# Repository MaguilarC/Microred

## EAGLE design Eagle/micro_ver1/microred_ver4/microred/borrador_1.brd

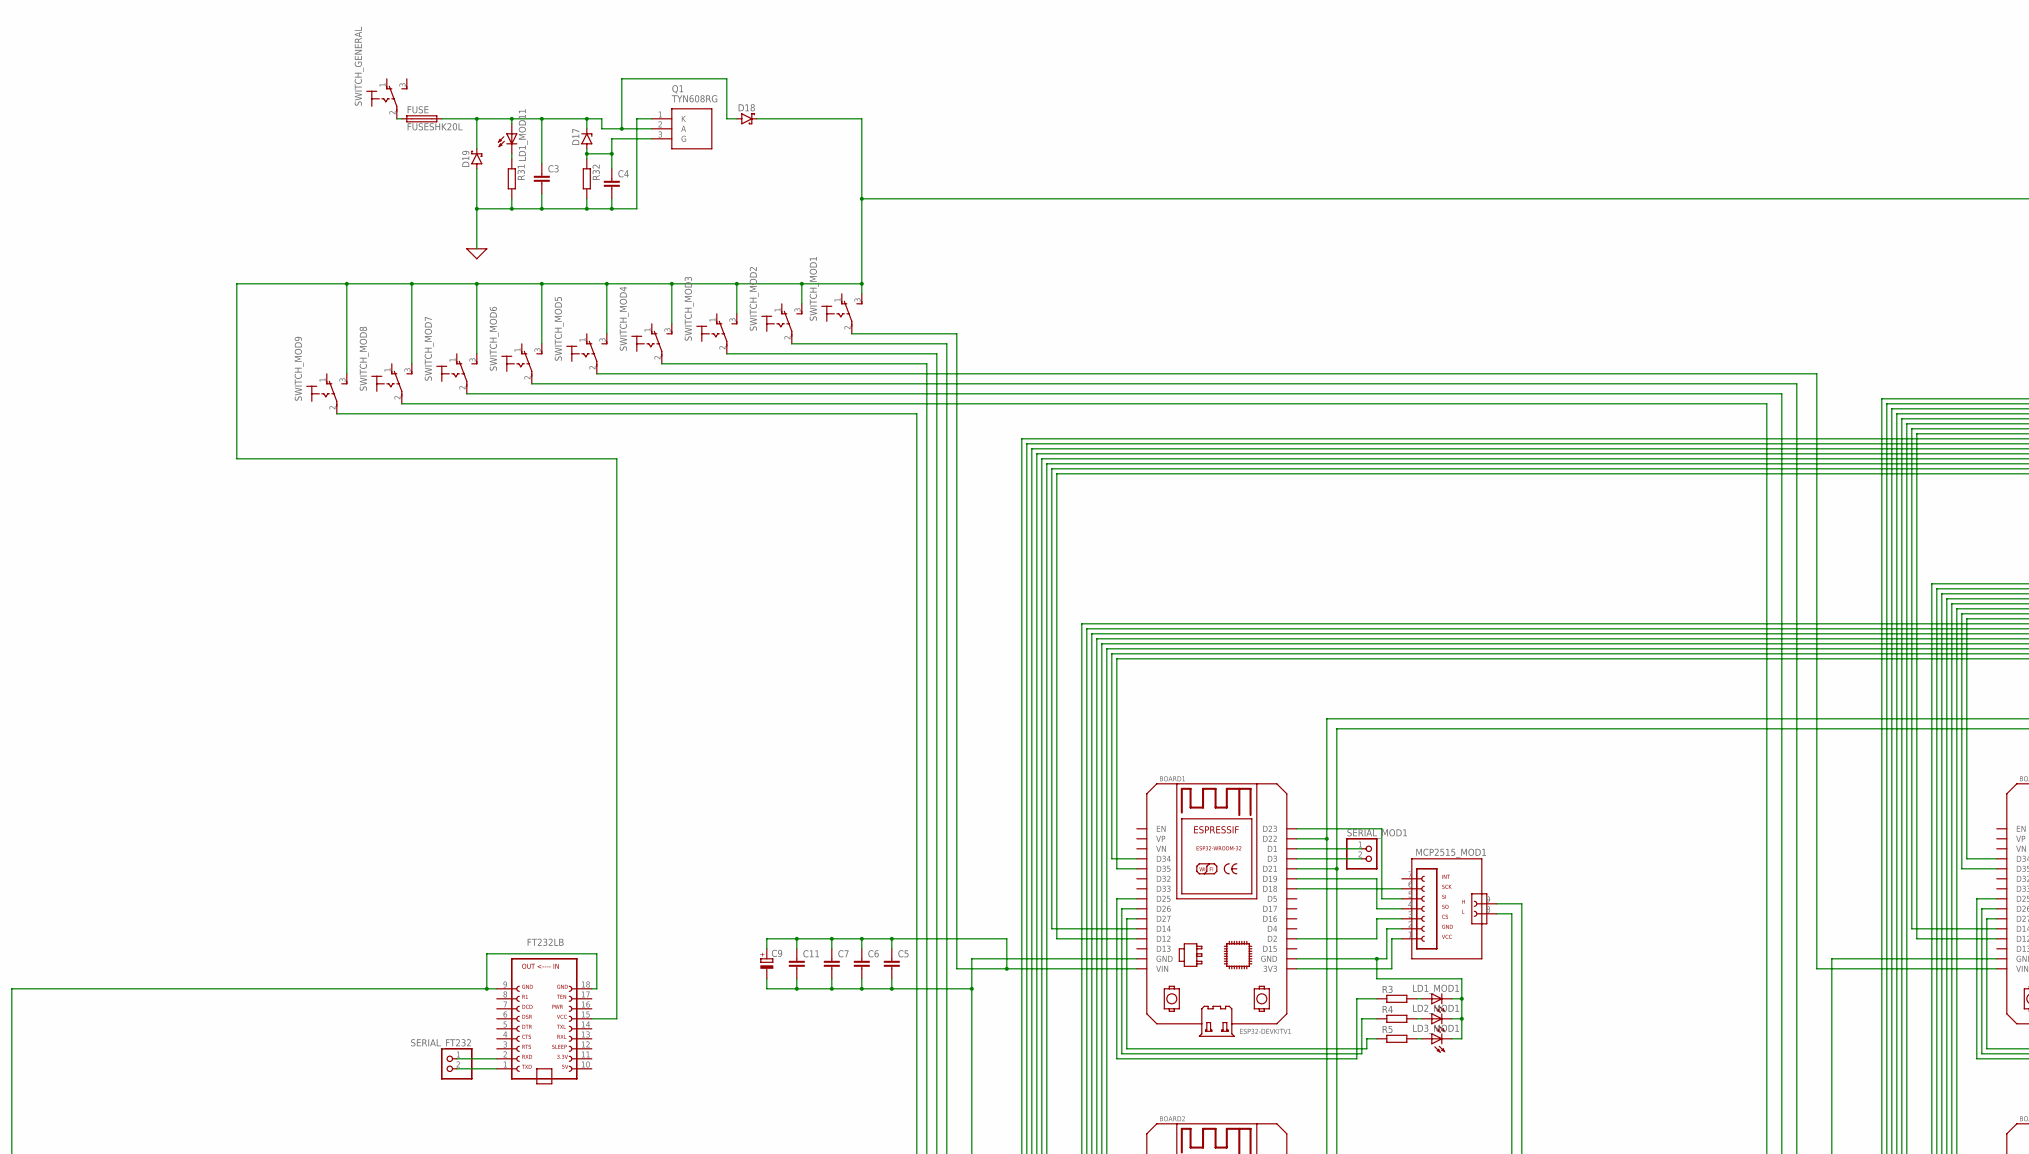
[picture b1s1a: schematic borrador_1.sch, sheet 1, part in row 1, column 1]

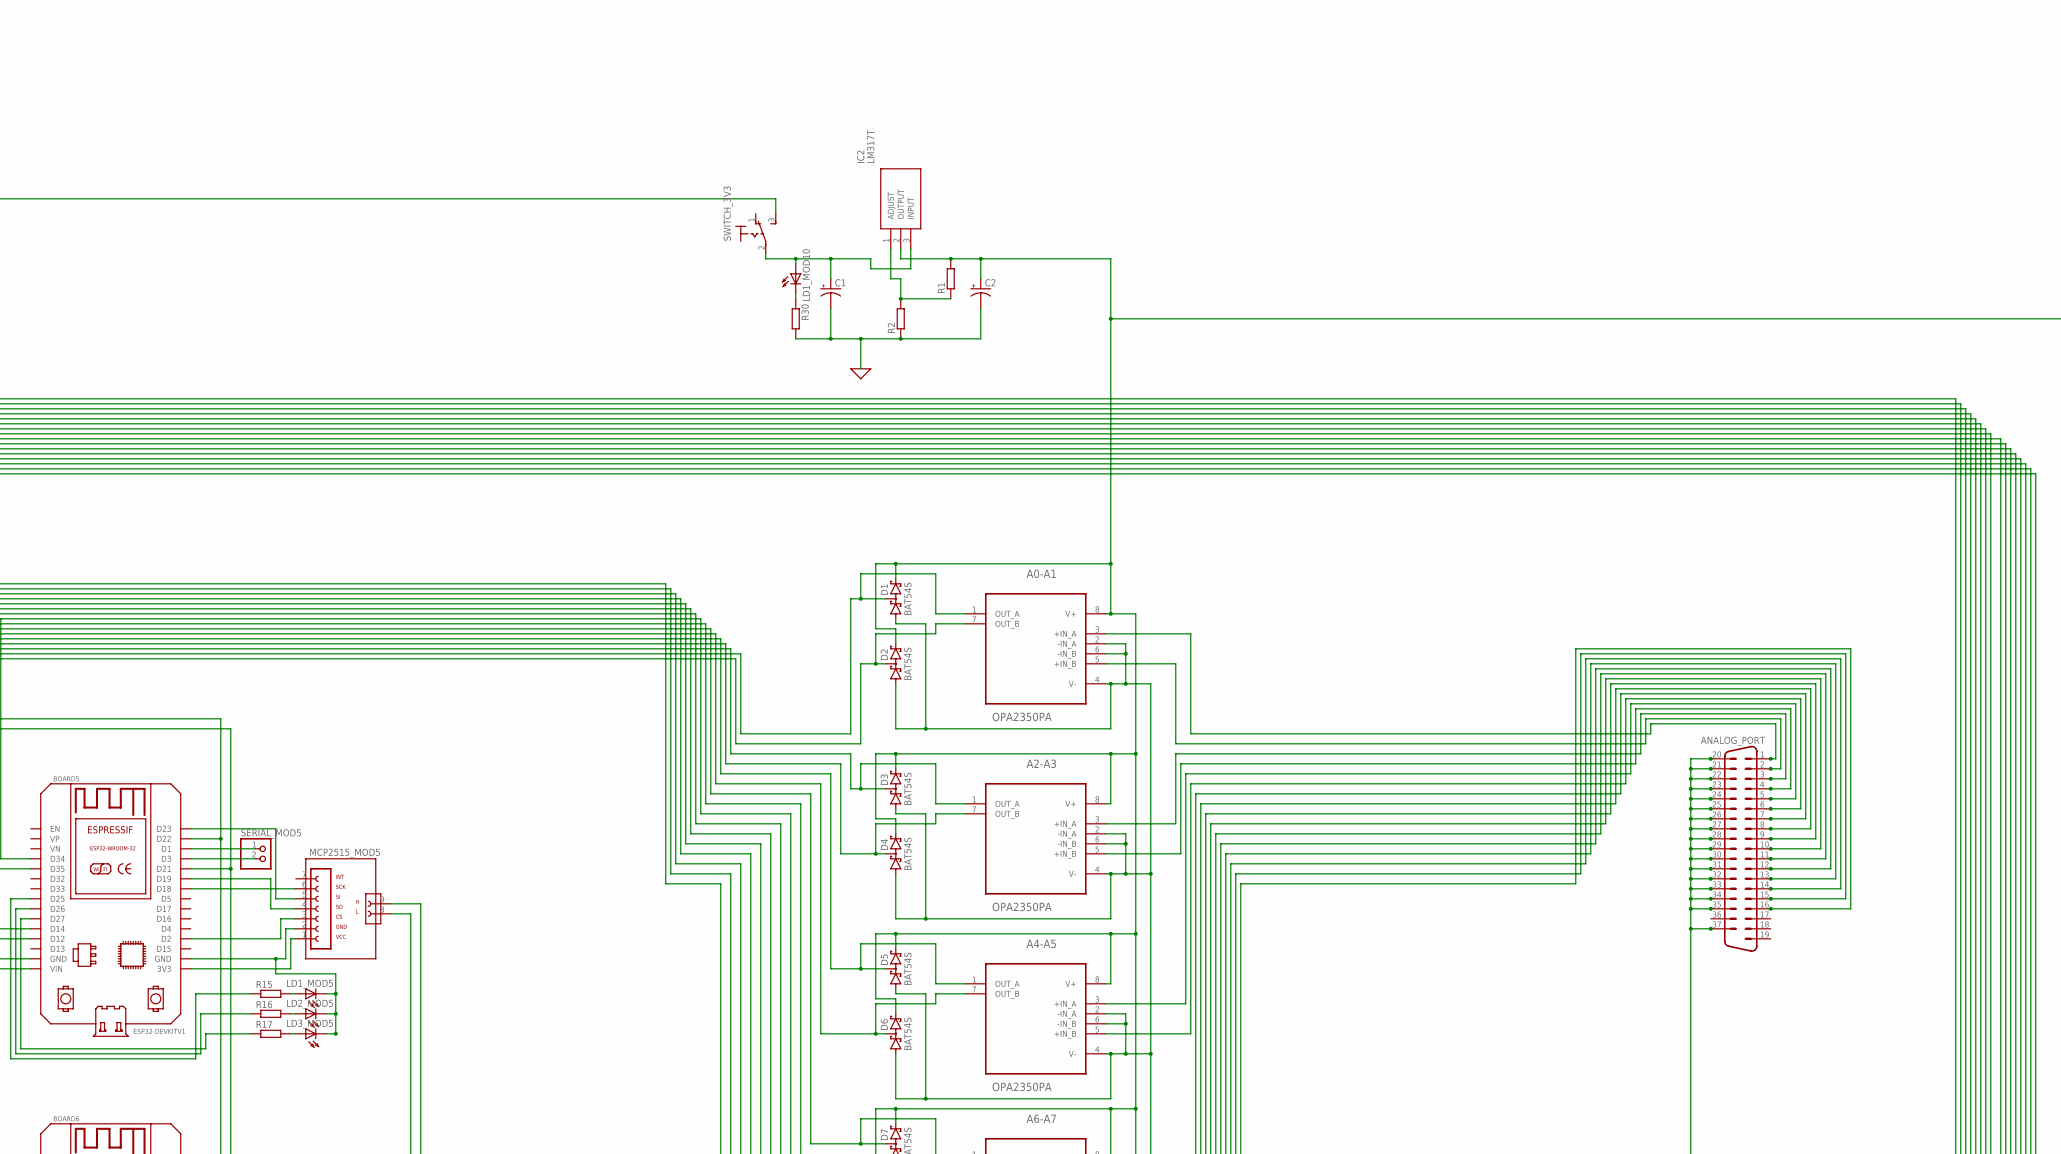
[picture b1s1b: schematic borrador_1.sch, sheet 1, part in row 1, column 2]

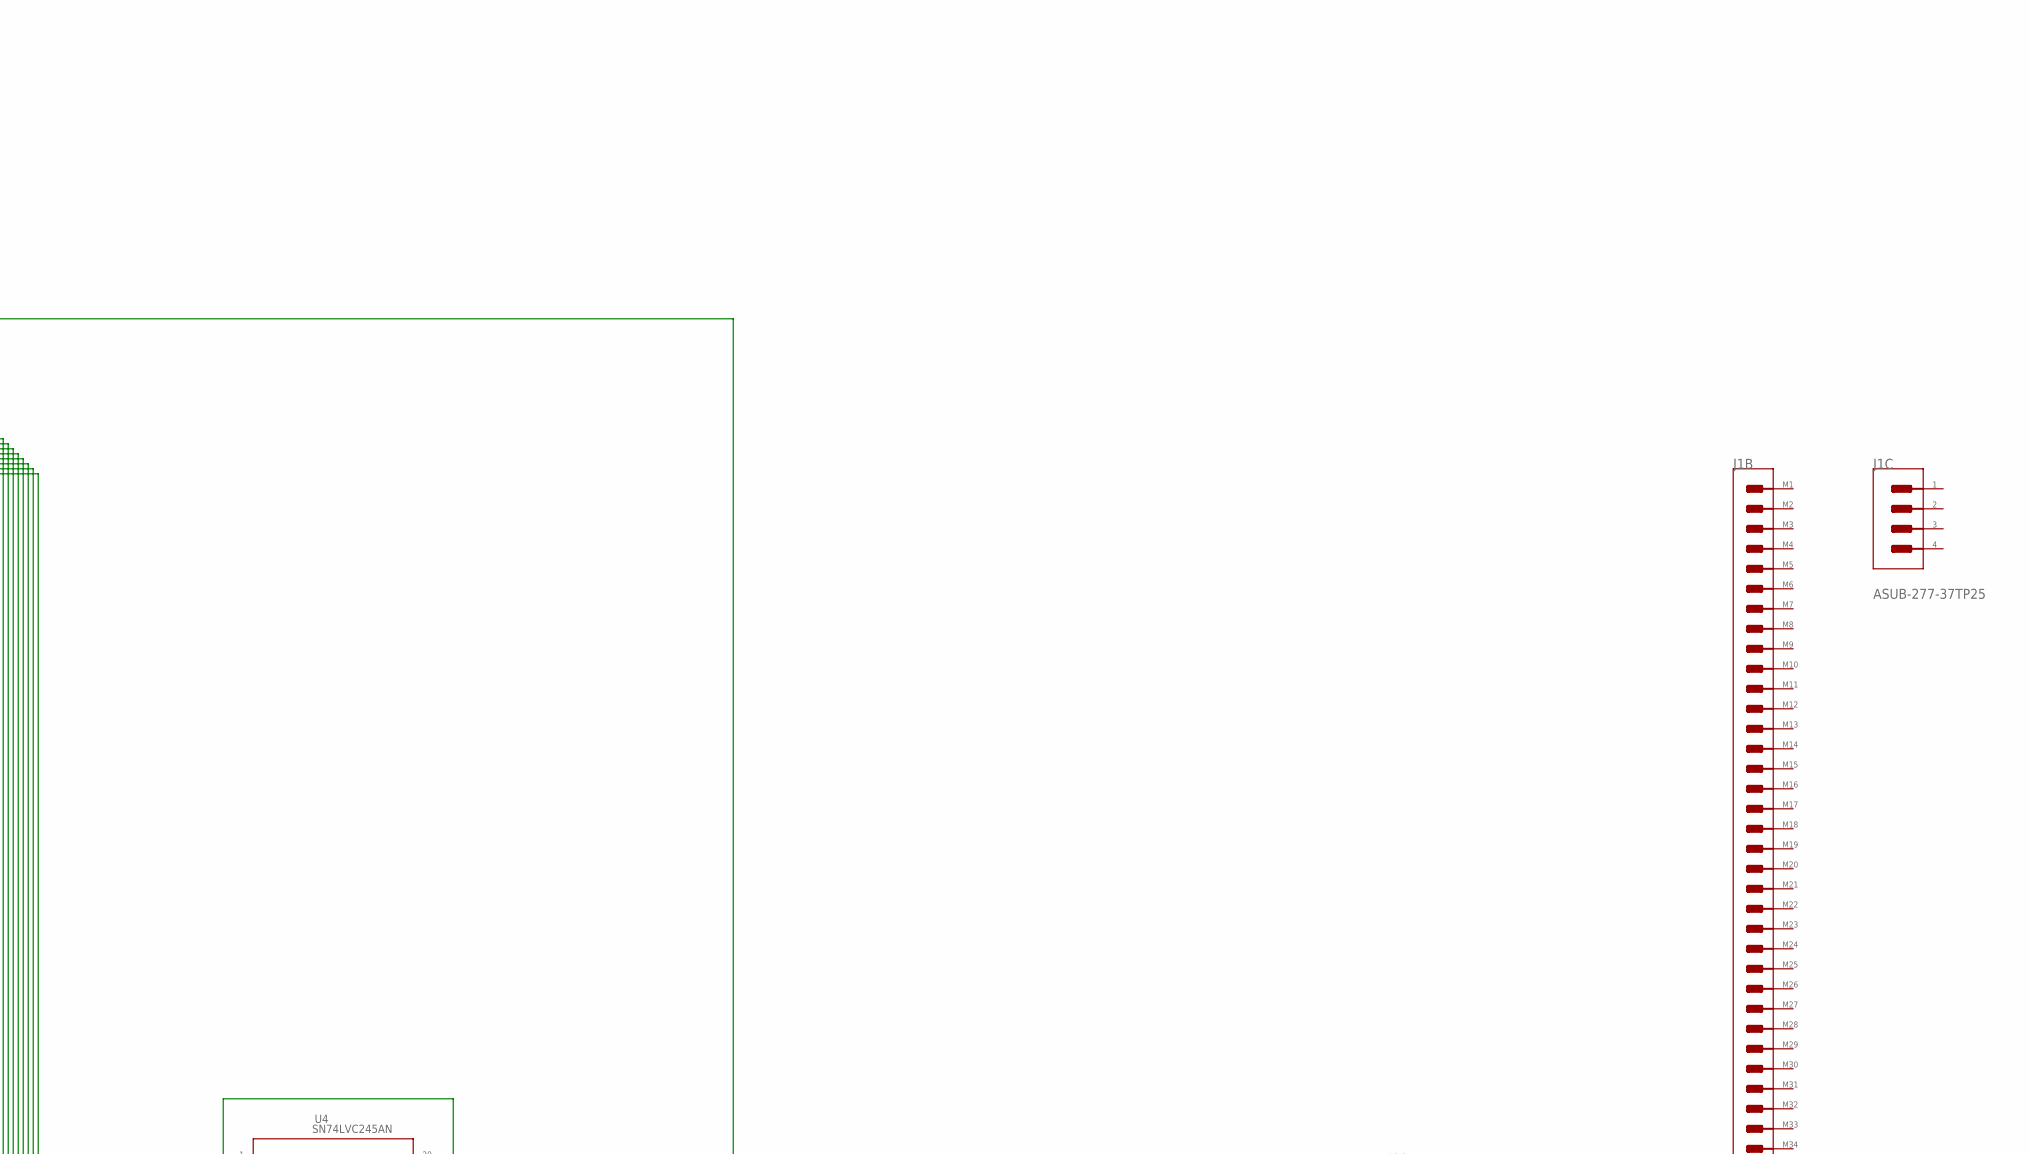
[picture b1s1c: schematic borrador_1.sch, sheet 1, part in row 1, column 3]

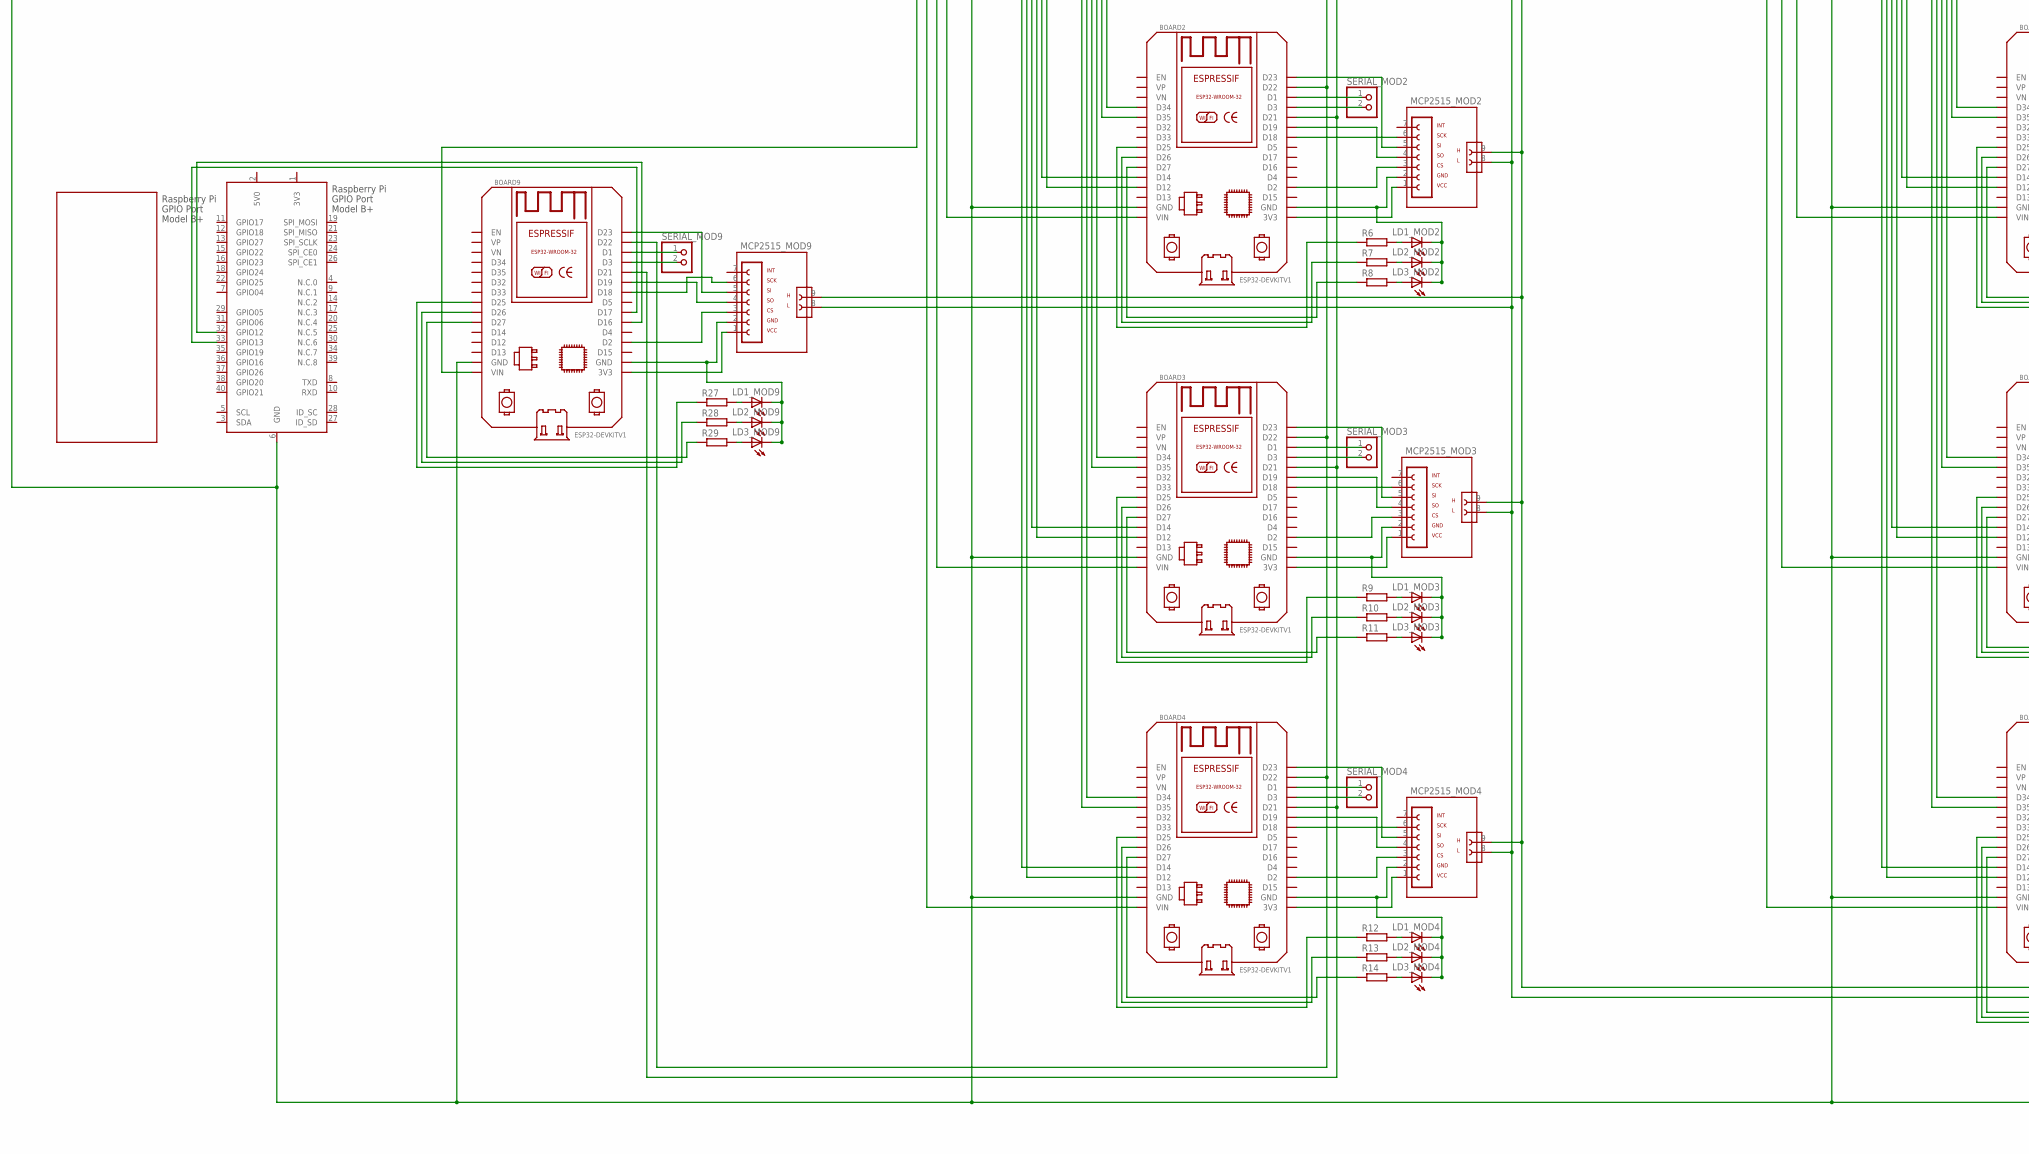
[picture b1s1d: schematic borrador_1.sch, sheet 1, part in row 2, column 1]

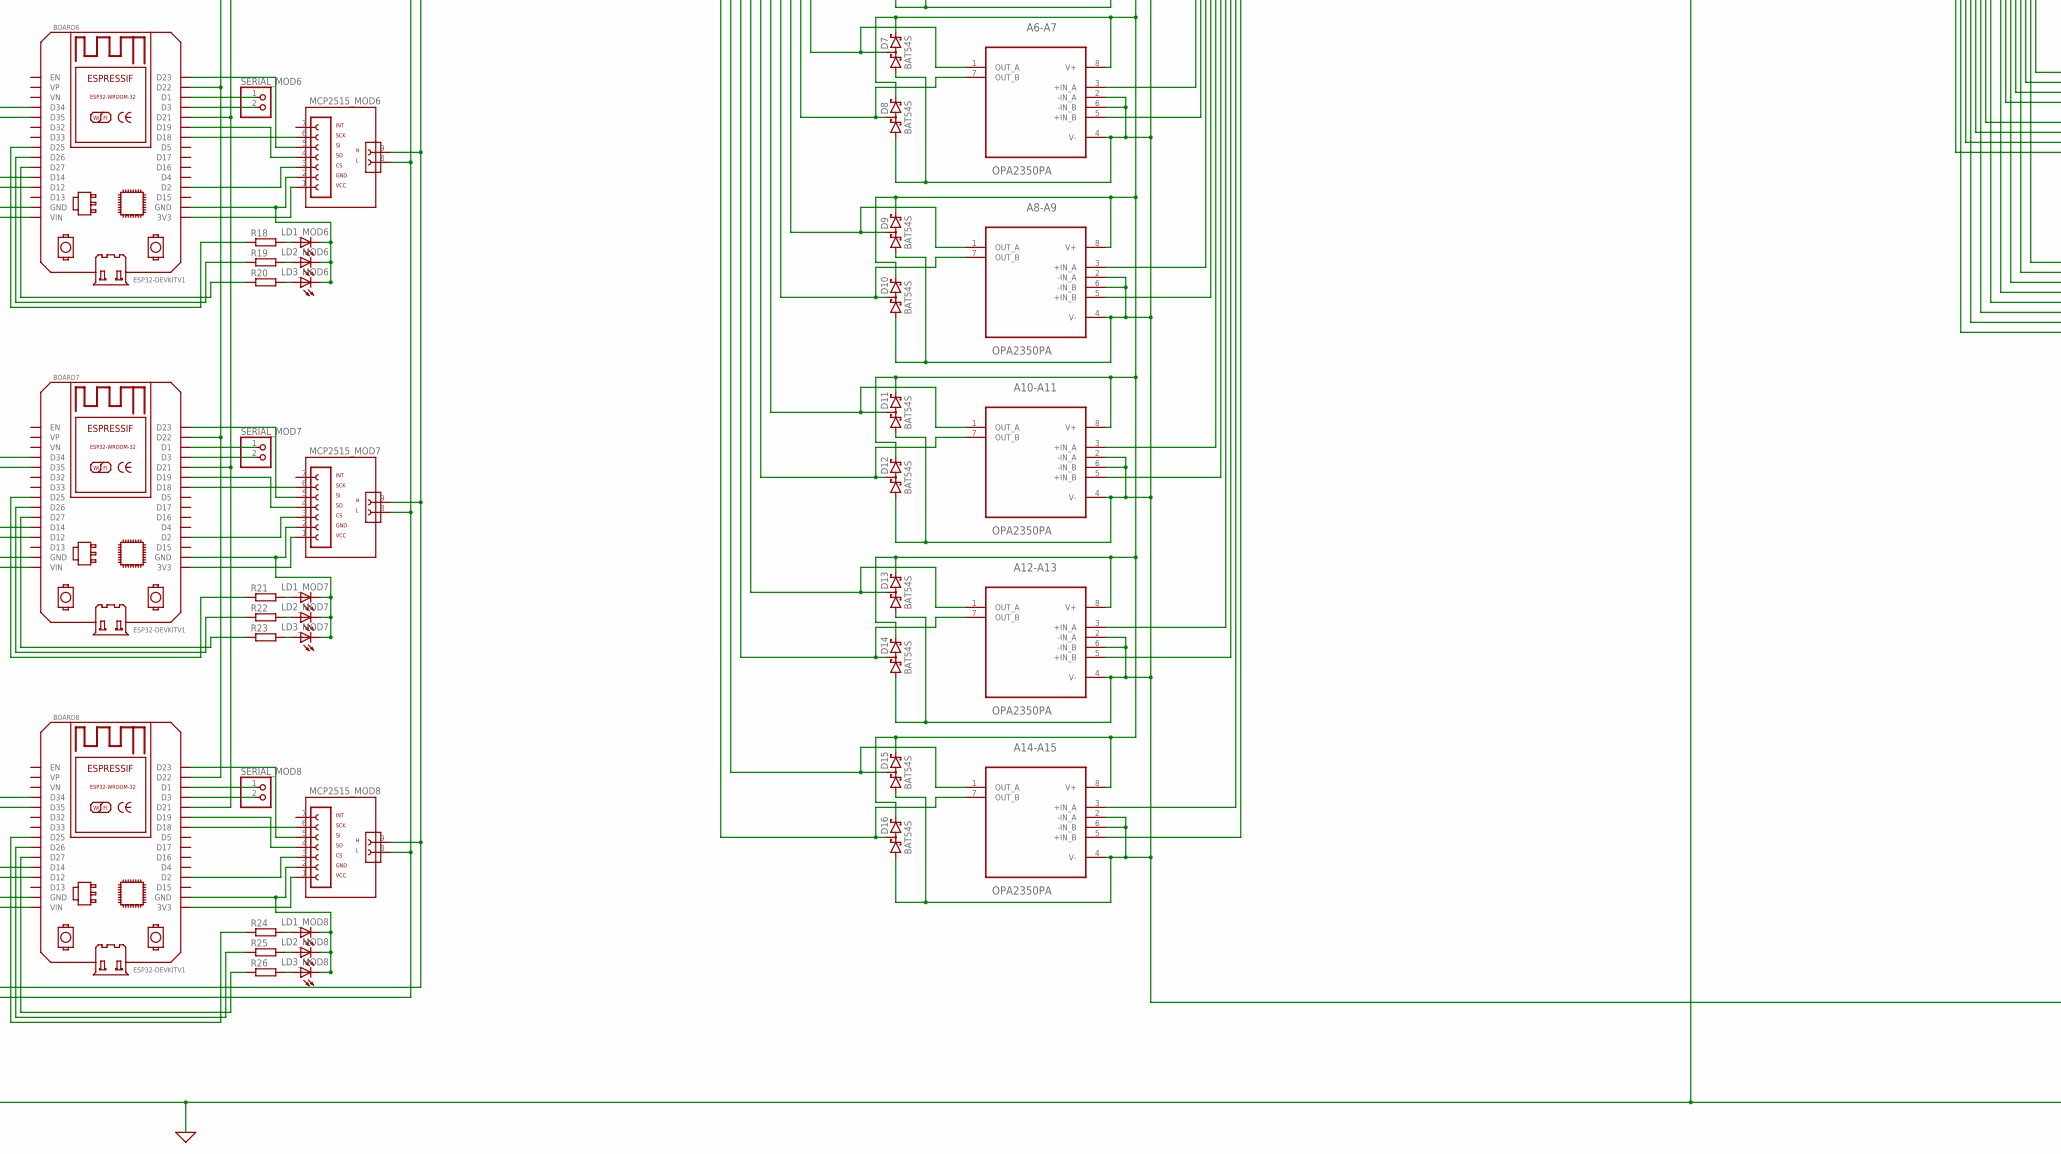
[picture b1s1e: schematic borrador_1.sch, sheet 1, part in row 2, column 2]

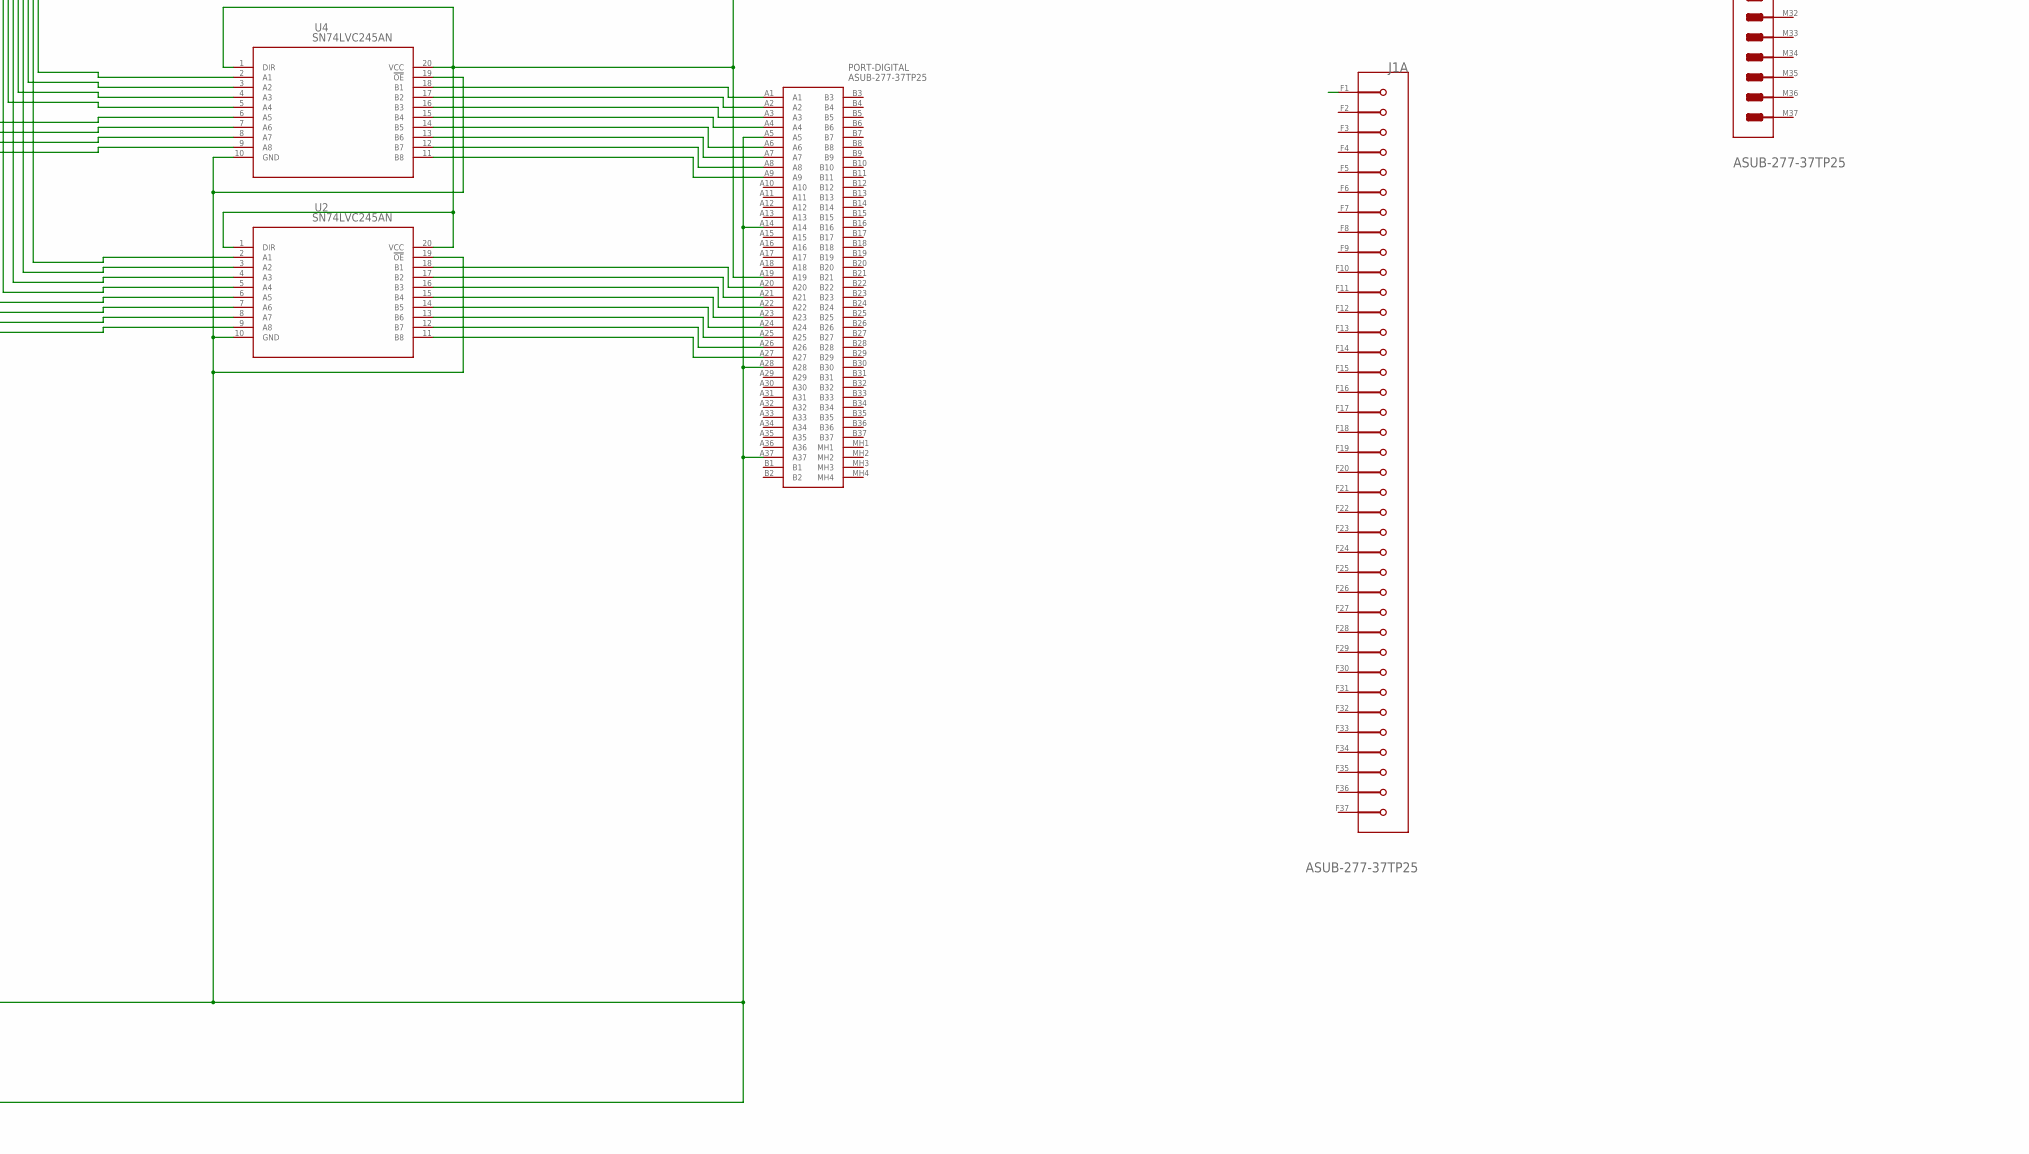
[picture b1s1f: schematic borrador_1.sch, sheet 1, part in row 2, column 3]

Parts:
A0-A1, A2-A3, A4-A5, A6-A7, A8-A9, A10-A11, A12-A13, A14-A15: OPA2350PA; DIP254P762X508-8
ANALOG_PORT: M37HP
BOARD1, BOARD2, BOARD3, BOARD4, BOARD5, BOARD6, BOARD7, BOARD8, BOARD9: ESP32DEVKITV1; ESP32-DEVKITV1
C1, C2: CPOL-USE2.5-6; E2,5-6
C3, C4, C11: C-EU050-030X075; C050-030X075
C5, C6: C2.5/2; C2.5-2
C7: C-EU025-030X050; C025-030X050
C9: CPOL-EUE2.5-6; E2,5-6
D1, D2, D3, D4, D5, D6, D7, D8, D9, D10, D11, D12, D13, D14, D15, D16: BAT54S; SOT23
D17: ZENER-DIODEDO41Z10; DO41Z10
D18, D19: SCHOTTKY-DIODECB429-15; CB429-15
FT232LB: FT232BL
FUSE: FUSESHK20L; SHK20L
IC2: LM317T; TO255P460X1020X2008-3P
J1: ASSMANN_WSW_COMPONENTS_ASUB-277-37TP25ASSMANN_WSW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; ASSMANN_WSW_COMPONENTS_ASUB-277-37TP25_0
LD1_MOD1, LD1_MOD2, LD1_MOD3, LD1_MOD4, LD1_MOD5, LD1_MOD6, LD1_MOD7, LD1_MOD8, LD1_MOD9, LD1_MOD10, LD1_MOD11, LD2_MOD1, LD2_MOD2, LD2_MOD3, LD2_MOD4, LD2_MOD5, LD2_MOD6, LD2_MOD7, LD2_MOD8, LD2_MOD9, LD3_MOD1, LD3_MOD2, LD3_MOD3, LD3_MOD4, LD3_MOD5, LD3_MOD6, LD3_MOD7, LD3_MOD8, LD3_MOD9: LED3MM
MCP2515_MOD1, MCP2515_MOD2, MCP2515_MOD3, MCP2515_MOD4, MCP2515_MOD5, MCP2515_MOD6, MCP2515_MOD7, MCP2515_MOD8, MCP2515_MOD9: MCP2515
PORT-DIGITAL: ASUB-277-37TP25; ASUB27737TP25
Q1: TYN608RG; TO270P460X1020X2008-3P
R1, R2: R-EU_0411/15; 0411/15
R3, R4, R5, R6, R7, R8, R9, R10, R11, R12, R13, R14, R15, R16, R17, R18, R19, R20, R21, R22, R23, R24, R25, R26, R27, R28, R29, R30, R31, R32: R-EU_0207/10; 0207/10
SERIAL_FT232: PINHD-1X2; 1X02
SERIAL_MOD1, SERIAL_MOD2, SERIAL_MOD3, SERIAL_MOD4, SERIAL_MOD5, SERIAL_MOD6, SERIAL_MOD7, SERIAL_MOD8, SERIAL_MOD9: PINHD-1X2; 1X02
SWITCH_3V3: M9040P
SWITCH_GENERAL: M9040P
SWITCH_MOD1, SWITCH_MOD2, SWITCH_MOD3, SWITCH_MOD4, SWITCH_MOD5, SWITCH_MOD6, SWITCH_MOD7, SWITCH_MOD8, SWITCH_MOD9: M9040P
U2, U4: SN74LVC245AN; N20
X1: RASPI_GPIO_B+_BOX
X2: RASPI_BOARD_B+#_F; RASPI_BOARD_B+_FULL

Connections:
3V3: X1.1 (3V3)
5V: D18.C, FT232LB.15, SWITCH_3V3.3 (S), SWITCH_MOD1.3 (S), SWITCH_MOD2.3 (S), SWITCH_MOD3.3 (S), SWITCH_MOD4.3 (S), SWITCH_MOD5.3 (S), SWITCH_MOD6.3 (S), SWITCH_MOD7.3 (S), SWITCH_MOD8.3 (S), SWITCH_MOD9.3 (S)
5V0: X1.2 (5V0)
5V_MOD1: BOARD1.VIN, C5.1, C6.1, C7.1, C9.+, C11.1, SWITCH_MOD1.2
5V_MOD2: BOARD2.VIN, SWITCH_MOD2.2
5V_MOD3: BOARD3.VIN, SWITCH_MOD3.2
5V_MOD4: BOARD4.VIN, SWITCH_MOD4.2
5V_MOD5: BOARD5.VIN, SWITCH_MOD5.2
5V_MOD6: BOARD6.VIN, SWITCH_MOD6.2
5V_MOD7: BOARD7.VIN, SWITCH_MOD7.2
5V_MOD8: BOARD8.VIN, SWITCH_MOD8.2
5V_MOD9: BOARD9.VIN, SWITCH_MOD9.2
CAN_H: MCP2515_MOD1.9, MCP2515_MOD2.9, MCP2515_MOD3.9, MCP2515_MOD4.9, MCP2515_MOD5.9, MCP2515_MOD6.9, MCP2515_MOD7.9, MCP2515_MOD8.9, MCP2515_MOD9.9
CAN_L: MCP2515_MOD1.8, MCP2515_MOD2.8, MCP2515_MOD3.8, MCP2515_MOD4.8, MCP2515_MOD5.8, MCP2515_MOD6.8, MCP2515_MOD7.8, MCP2515_MOD8.8, MCP2515_MOD9.8
GND_MOD1: BOARD1.GND@1 (GND), LD1_MOD1.K (C), LD2_MOD1.K (C), LD3_MOD1.K (C), MCP2515_MOD1.2
GND_MOD2: BOARD2.GND@1 (GND), LD1_MOD2.K (C), LD2_MOD2.K (C), LD3_MOD2.K (C), MCP2515_MOD2.2
GND_MOD3: BOARD3.GND@1 (GND), LD1_MOD3.K (C), LD2_MOD3.K (C), LD3_MOD3.K (C), MCP2515_MOD3.2
GND_MOD4: BOARD4.GND@1 (GND), LD1_MOD4.K (C), LD2_MOD4.K (C), LD3_MOD4.K (C), MCP2515_MOD4.2
GND_MOD5: BOARD5.GND@1 (GND), LD1_MOD5.K (C), LD2_MOD5.K (C), LD3_MOD5.K (C), MCP2515_MOD5.2
GND_MOD6: BOARD6.GND@1 (GND), LD1_MOD6.K (C), LD2_MOD6.K (C), LD3_MOD6.K (C), MCP2515_MOD6.2
GND_MOD7: BOARD7.GND@1 (GND), LD1_MOD7.K (C), LD2_MOD7.K (C), LD3_MOD7.K (C), MCP2515_MOD7.2
GND_MOD8: BOARD8.GND@1 (GND), LD1_MOD8.K (C), LD2_MOD8.K (C), LD3_MOD8.K (C), MCP2515_MOD8.2
GND_MOD9: BOARD9.GND@1 (GND), LD1_MOD9.K (C), LD2_MOD9.K (C), LD3_MOD9.K (C), MCP2515_MOD9.2
L_3V3: A0-A1.8 (V+), A2-A3.8 (V+), A4-A5.8 (V+), A6-A7.8 (V+), A8-A9.8 (V+), A10-A11.8 (V+), A12-A13.8 (V+), A14-A15.8 (V+), C2.+, D1.2 (C2), D2.2 (C2), D3.2 (C2), D4.2 (C2), D5.2 (C2), D6.2 (C2), D7.2 (C2), D8.2 (C2), D9.2 (C2), D10.2 (C2), D11.2 (C2), D12.2 (C2), D13.2 (C2), D14.2 (C2), D15.2 (C2), D16.2 (C2), IC2.2 (OUTPUT), PORT-DIGITAL.A19, R1.2, U2.1 (DIR), U2.20 (VCC), U4.1 (DIR), U4.20 (VCC)
L_AO_0: A0-A1.1 (OUT_A), BOARD1.D34, D1.3 (C1A2)
L_AO_0_P: A0-A1.3 (+IN_A), ANALOG_PORT.1
L_AO_1: A0-A1.7 (OUT_B), BOARD1.D35, D2.3 (C1A2)
L_AO_1_P: A0-A1.5 (+IN_B), ANALOG_PORT.2
L_AO_2: A2-A3.1 (OUT_A), BOARD2.D34, D3.3 (C1A2)
L_AO_2_P: A2-A3.3 (+IN_A), ANALOG_PORT.3
L_AO_3: A2-A3.7 (OUT_B), BOARD2.D35, D4.3 (C1A2)
L_AO_3_P: A2-A3.5 (+IN_B), ANALOG_PORT.4
L_AO_4: A4-A5.1 (OUT_A), BOARD3.D34, D5.3 (C1A2)
L_AO_4_P: A4-A5.3 (+IN_A), ANALOG_PORT.5
L_AO_5: A4-A5.7 (OUT_B), BOARD3.D35, D6.3 (C1A2)
L_AO_5_P: A4-A5.5 (+IN_B), ANALOG_PORT.6
L_AO_6: A6-A7.1 (OUT_A), BOARD4.D34, D7.3 (C1A2)
L_AO_6_P: A6-A7.3 (+IN_A), ANALOG_PORT.7
L_AO_7: A6-A7.7 (OUT_B), BOARD4.D35, D8.3 (C1A2)
L_AO_7_P: A6-A7.5 (+IN_B), ANALOG_PORT.8
L_AO_8: A8-A9.1 (OUT_A), BOARD5.D34, D9.3 (C1A2)
L_AO_8_P: A8-A9.3 (+IN_A), ANALOG_PORT.9
L_AO_9: A8-A9.7 (OUT_B), BOARD5.D35, D10.3 (C1A2)
L_AO_9_P: A8-A9.5 (+IN_B), ANALOG_PORT.10
L_AO_10: A10-A11.1 (OUT_A), BOARD6.D34, D11.3 (C1A2)
L_AO_10_P: A10-A11.3 (+IN_A), ANALOG_PORT.11
L_AO_11: A10-A11.7 (OUT_B), BOARD6.D35, D12.3 (C1A2)
L_AO_11_P: A10-A11.5 (+IN_B), ANALOG_PORT.12
L_AO_12: A12-A13.1 (OUT_A), BOARD7.D34, D13.3 (C1A2)
L_AO_12_P: A12-A13.3 (+IN_A), ANALOG_PORT.13
L_AO_13: A12-A13.7 (OUT_B), BOARD7.D35, D14.3 (C1A2)
L_AO_13_P: A12-A13.5 (+IN_B), ANALOG_PORT.14
L_AO_14: A14-A15.1 (OUT_A), BOARD8.D34, D15.3 (C1A2)
L_AO_14_P: A14-A15.3 (+IN_A), ANALOG_PORT.15
L_AO_15: A14-A15.7 (OUT_B), BOARD8.D35, D16.3 (C1A2)
L_AO_15_P: A14-A15.5 (+IN_B), ANALOG_PORT.16
L_DI_0: BOARD1.D12, U4.2 (A1)
L_DI_0_P: PORT-DIGITAL.A1, U4.18 (B1)
L_DI_1: BOARD1.D14, U2.2 (A1)
L_DI_1_P: PORT-DIGITAL.A20, U2.18 (B1)
L_DI_2: BOARD2.D12, U4.3 (A2)
L_DI_2_P: PORT-DIGITAL.A2, U4.17 (B2)
L_DI_3: BOARD2.D14, U2.3 (A2)
L_DI_3_P: PORT-DIGITAL.A21, U2.17 (B2)
L_DI_4: BOARD3.D12, U4.4 (A3)
L_DI_4_P: PORT-DIGITAL.A3, U4.16 (B3)
L_DI_5: BOARD3.D14, U2.4 (A3)
L_DI_5_P: PORT-DIGITAL.A22, U2.16 (B3)
L_DI_6: BOARD4.D12, U4.5 (A4)
L_DI_6_P: PORT-DIGITAL.A4, U4.15 (B4)
L_DI_7: BOARD4.D14, U2.5 (A4)
L_DI_7_P: PORT-DIGITAL.A23, U2.15 (B4)
L_DI_8: BOARD5.D12, U2.6 (A5)
L_DI_8_P: PORT-DIGITAL.A24, U2.14 (B5)
L_DI_9: BOARD5.D14, U4.6 (A5)
L_DI_9_P: PORT-DIGITAL.A6, U4.14 (B5)
L_DI_10: BOARD6.D12, U2.7 (A6)
L_DI_10_P: PORT-DIGITAL.A25, U2.13 (B6)
L_DI_11: BOARD6.D14, U4.7 (A6)
L_DI_11_P: PORT-DIGITAL.A7, U4.13 (B6)
L_DI_012: BOARD7.D12, U2.8 (A7)
L_DI_12_P: PORT-DIGITAL.A26, U2.12 (B7)
L_DI_13: BOARD7.D14, U4.8 (A7)
L_DI_13_P: PORT-DIGITAL.A8, U4.12 (B7)
L_DI_014: BOARD8.D12, U2.9 (A8)
L_DI_14_P: PORT-DIGITAL.A27, U2.11 (B8)
L_DI_015: BOARD8.D14, U4.9 (A8)
L_DI_15_P: PORT-DIGITAL.A9, U4.11 (B8)
L_GROUND: A0-A1.2 (-IN_A), A0-A1.4 (V-), A0-A1.6 (-IN_B), A2-A3.2 (-IN_A), A2-A3.4 (V-), A2-A3.6 (-IN_B), A4-A5.2 (-IN_A), A4-A5.4 (V-), A4-A5.6 (-IN_B), A6-A7.2 (-IN_A), A6-A7.4 (V-), A6-A7.6 (-IN_B), A8-A9.2 (-IN_A), A8-A9.4 (V-), A8-A9.6 (-IN_B), A10-A11.2 (-IN_A), A10-A11.4 (V-), A10-A11.6 (-IN_B), A12-A13.2 (-IN_A), A12-A13.4 (V-), A12-A13.6 (-IN_B), A14-A15.2 (-IN_A), A14-A15.4 (V-), A14-A15.6 (-IN_B), ANALOG_PORT.20, ANALOG_PORT.21, ANALOG_PORT.22, ANALOG_PORT.23, ANALOG_PORT.24, ANALOG_PORT.25, ANALOG_PORT.26, ANALOG_PORT.27, ANALOG_PORT.28, ANALOG_PORT.29, ANALOG_PORT.30, ANALOG_PORT.31, ANALOG_PORT.32, ANALOG_PORT.33, ANALOG_PORT.34, ANALOG_PORT.35, ANALOG_PORT.37, BOARD1.GND, BOARD2.GND, BOARD3.GND, BOARD4.GND, BOARD5.GND, BOARD6.GND, BOARD7.GND, BOARD8.GND, BOARD9.GND, C1.-, C2.-, C3.2, C4.2, C5.2, C6.2, C7.2, C9.-, C11.2, D1.1 (A1), D2.1 (A1), D3.1 (A1), D4.1 (A1), D5.1 (A1), D6.1 (A1), D7.1 (A1), D8.1 (A1), D9.1 (A1), D10.1 (A1), D11.1 (A1), D12.1 (A1), D13.1 (A1), D14.1 (A1), D15.1 (A1), D16.1 (A1), D19.A, FT232LB.9, FT232LB.18, PORT-DIGITAL.A5, PORT-DIGITAL.A14, PORT-DIGITAL.A28, PORT-DIGITAL.A37, Q1.1 (K), R2.1, R30.2, R31.2, R32.2, U2.10 (GND), U2.19 (!OE), U4.10 (GND), U4.19 (!OE), X1.6 (GND)
L_SCL: BOARD1.D22, BOARD2.D22, BOARD3.D22, BOARD4.D22, BOARD5.D22, BOARD6.D22, BOARD7.D22, BOARD8.D22, BOARD9.D22
L_SDA: BOARD1.D21, BOARD2.D21, BOARD3.D21, BOARD4.D21, BOARD5.D21, BOARD6.D21, BOARD7.D21, BOARD8.D21, BOARD9.D21
unnamed: C1.+, IC2.3 (INPUT), LD1_MOD10.A, SWITCH_3V3.2
unnamed: BOARD7.3V3, MCP2515_MOD7.1
unnamed: IC2.1 (ADJUST), R1.1, R2.2
unnamed: LD1_MOD11.K (C), R31.1
unnamed: C4.1, D17.A, Q1.3 (G), R32.1
unnamed: BOARD9.D23, MCP2515_MOD9.5
unnamed: BOARD9.D19, MCP2515_MOD9.4
unnamed: LD1_MOD10.K (C), R30.1
unnamed: C3.1, D17.C, D18.A, D19.C, FUSE.2A (2), LD1_MOD11.A, Q1.2 (A)
unnamed: FUSE.1A (1), SWITCH_GENERAL.2
unnamed: BOARD1.D23, MCP2515_MOD1.5
unnamed: BOARD1.D19, MCP2515_MOD1.4
unnamed: BOARD1.D18, MCP2515_MOD1.6
unnamed: BOARD1.3V3, MCP2515_MOD1.1
unnamed: BOARD9.3V3, MCP2515_MOD9.1
unnamed: BOARD9.D18, MCP2515_MOD9.6
unnamed: BOARD9.D2, MCP2515_MOD9.3
unnamed: LD1_MOD2.A, R6.2
unnamed: BOARD1.D2, MCP2515_MOD1.3
unnamed: BOARD2.D18, MCP2515_MOD2.6
unnamed: BOARD2.D23, MCP2515_MOD2.5
unnamed: BOARD2.D19, MCP2515_MOD2.4
unnamed: BOARD2.3V3, MCP2515_MOD2.1
unnamed: LD1_MOD4.A, R12.2
unnamed: BOARD2.D2, MCP2515_MOD2.3
unnamed: BOARD3.D23, MCP2515_MOD3.5
unnamed: BOARD3.D18, MCP2515_MOD3.6
unnamed: BOARD3.D19, MCP2515_MOD3.4
unnamed: BOARD3.3V3, MCP2515_MOD3.1
unnamed: LD2_MOD4.A, R13.2
unnamed: BOARD3.D2, MCP2515_MOD3.3
unnamed: BOARD4.D18, MCP2515_MOD4.6
unnamed: BOARD4.D23, MCP2515_MOD4.5
unnamed: BOARD4.D19, MCP2515_MOD4.4
unnamed: BOARD4.3V3, MCP2515_MOD4.1
unnamed: BOARD4.D27, R14.1
unnamed: BOARD4.D2, MCP2515_MOD4.3
unnamed: LD1_MOD1.A, R3.2
unnamed: BOARD5.D18, MCP2515_MOD5.6
unnamed: BOARD5.D23, MCP2515_MOD5.5
unnamed: BOARD5.D19, MCP2515_MOD5.4
unnamed: BOARD5.3V3, MCP2515_MOD5.1
unnamed: LD1_MOD9.A, R27.2
unnamed: BOARD5.D2, MCP2515_MOD5.3
unnamed: BOARD6.D18, MCP2515_MOD6.6
unnamed: BOARD6.D23, MCP2515_MOD6.5
unnamed: BOARD6.D19, MCP2515_MOD6.4
unnamed: BOARD6.3V3, MCP2515_MOD6.1
unnamed: LD2_MOD9.A, R28.2
unnamed: BOARD6.D2, MCP2515_MOD6.3
unnamed: BOARD7.D18, MCP2515_MOD7.6
unnamed: BOARD7.D23, MCP2515_MOD7.5
unnamed: BOARD7.D19, MCP2515_MOD7.4
unnamed: LD3_MOD9.A, R29.2
unnamed: BOARD7.D2, MCP2515_MOD7.3
unnamed: BOARD8.D18, MCP2515_MOD8.6
unnamed: BOARD8.D23, MCP2515_MOD8.5
unnamed: BOARD8.D19, MCP2515_MOD8.4
unnamed: BOARD8.3V3, MCP2515_MOD8.1
unnamed: BOARD9.D27, R29.1
unnamed: BOARD8.D2, MCP2515_MOD8.3
unnamed: LD2_MOD1.A, R4.2
unnamed: LD3_MOD1.A, R5.2
unnamed: BOARD1.D27, R5.1
unnamed: BOARD1.D26, R4.1
unnamed: BOARD1.D25, R3.1
unnamed: LD2_MOD2.A, R7.2
unnamed: LD3_MOD2.A, R8.2
unnamed: BOARD2.D27, R8.1
unnamed: BOARD2.D26, R7.1
unnamed: BOARD2.D25, R6.1
unnamed: LD1_MOD3.A, R9.2
unnamed: LD2_MOD3.A, R10.2
unnamed: LD3_MOD3.A, R11.2
unnamed: LD3_MOD4.A, R14.2
unnamed: BOARD4.D26, R13.1
unnamed: BOARD4.D25, R12.1
unnamed: BOARD3.D27, R11.1
unnamed: BOARD3.D26, R10.1
unnamed: BOARD3.D25, R9.1
unnamed: LD1_MOD5.A, R15.2
unnamed: LD2_MOD5.A, R16.2
unnamed: LD3_MOD5.A, R17.2
unnamed: BOARD5.D27, R17.1
unnamed: BOARD5.D26, R16.1
unnamed: BOARD5.D25, R15.1
unnamed: LD1_MOD6.A, R18.2
unnamed: LD2_MOD6.A, R19.2
unnamed: LD3_MOD6.A, R20.2
unnamed: BOARD6.D27, R20.1
unnamed: BOARD6.D26, R19.1
unnamed: BOARD6.D25, R18.1
unnamed: LD1_MOD7.A, R21.2
unnamed: LD2_MOD7.A, R22.2
unnamed: LD3_MOD7.A, R23.2
unnamed: BOARD7.D27, R23.1
unnamed: BOARD7.D26, R22.1
unnamed: BOARD7.D25, R21.1
unnamed: LD1_MOD8.A, R24.2
unnamed: LD2_MOD8.A, R25.2
unnamed: LD3_MOD8.A, R26.2
unnamed: BOARD8.D27, R26.1
unnamed: BOARD8.D26, R25.1
unnamed: BOARD8.D25, R24.1
unnamed: BOARD9.D26, R28.1
unnamed: BOARD9.D25, R27.1
RX_FT232BL: FT232LB.2, SERIAL_FT232.1
TX_FT232BL: FT232LB.1, SERIAL_FT232.2
U0_RX_MOD1: BOARD1.D3, SERIAL_MOD1.2
U0_RX_MOD2: BOARD2.D3, SERIAL_MOD2.2
U0_RX_MOD3: BOARD3.D3, SERIAL_MOD3.2
U0_RX_MOD4: BOARD4.D3, SERIAL_MOD4.2
U0_RX_MOD5: BOARD5.D3, SERIAL_MOD5.2
U0_RX_MOD6: BOARD6.D3, SERIAL_MOD6.2
U0_RX_MOD7: BOARD7.D3, SERIAL_MOD7.2
U0_RX_MOD8: BOARD8.D3, SERIAL_MOD8.2
U0_RX_MOD9: BOARD9.D3, SERIAL_MOD9.2
U0_TX_MOD1: BOARD1.D1, SERIAL_MOD1.1
U0_TX_MOD2: BOARD2.D1, SERIAL_MOD2.1
U0_TX_MOD3: BOARD3.D1, SERIAL_MOD3.1
U0_TX_MOD4: BOARD4.D1, SERIAL_MOD4.1
U0_TX_MOD5: BOARD5.D1, SERIAL_MOD5.1
U0_TX_MOD6: BOARD6.D1, SERIAL_MOD6.1
U0_TX_MOD7: BOARD7.D1, SERIAL_MOD7.1
U0_TX_MOD8: BOARD8.D1, SERIAL_MOD8.1
U0_TX_MOD9: BOARD9.D1, SERIAL_MOD9.1
U2_RX_MOD9: BOARD9.D16, X1.32 (GPIO12)
U2_TX_MOD9: BOARD9.D17, X1.33 (GPIO13)

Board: 2 copper layers, 147 parts (0 on the bottom side), 217 nets, no tracks yet.

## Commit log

2021-10-27 Subida de archivos
